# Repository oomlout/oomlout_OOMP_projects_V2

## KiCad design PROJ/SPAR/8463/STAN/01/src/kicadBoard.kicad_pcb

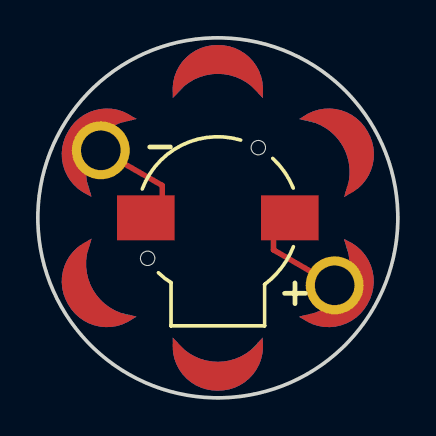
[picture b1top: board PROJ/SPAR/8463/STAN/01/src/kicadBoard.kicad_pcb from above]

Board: 2 copper layers, 20.0 x 20.0 mm, 8 parts (1 on the bottom side), 2 nets.

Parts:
B1: Buzzer; BUZZER-CCV
U$1, U$4, U$6, U$7: SEWTAP-NOHOLE2; PETAL-NOHOLE-2SIDE
U$2: LOGO-LPLP; LOGO-LILYPAD
U$8, U$9: SEWTAP6; PETAL-SMALL-2SIDE

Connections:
+: B1.+, U$9.1
-: B1.-, U$8.1

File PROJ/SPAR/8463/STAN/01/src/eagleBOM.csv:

"Part";"Value";"Device";"Package";"Description";"";
"B1";"Buzzer";"BUZZERSMD2";"BUZZER-CCV";"Buzzer 12mm";"";
"U$1";"SEWTAP-NOHOLE2";"SEWTAP-NOHOLE2";"PETAL-NOHOLE-2SIDE";"";"";
"U$2";"LOGO-LPLP";"LOGO-LPLP";"LOGO-LILYPAD";"";"";
"U$4";"SEWTAP-NOHOLE2";"SEWTAP-NOHOLE2";"PETAL-NOHOLE-2SIDE";"";"";
"U$6";"SEWTAP-NOHOLE2";"SEWTAP-NOHOLE2";"PETAL-NOHOLE-2SIDE";"";"";
"U$7";"SEWTAP-NOHOLE2";"SEWTAP-NOHOLE2";"PETAL-NOHOLE-2SIDE";"";"";
"U$8";"SEWTAP6";"SEWTAP6";"PETAL-SMALL-2SIDE";"";"";
"U$9";"SEWTAP6";"SEWTAP6";"PETAL-SMALL-2SIDE";"";"";

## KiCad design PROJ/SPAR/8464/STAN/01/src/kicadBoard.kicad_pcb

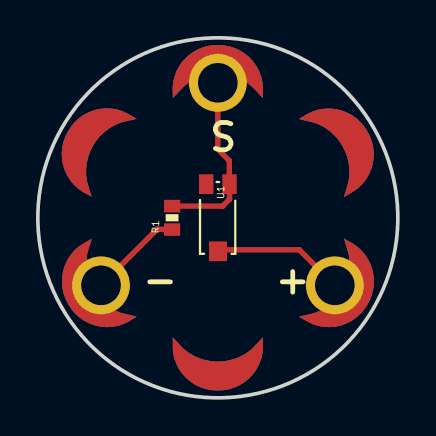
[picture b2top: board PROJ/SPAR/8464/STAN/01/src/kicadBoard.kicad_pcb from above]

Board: 2 copper layers, 20.0 x 20.0 mm, 9 parts (1 on the bottom side), 3 nets.

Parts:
LIGHT1, LIGHT2, LIGHT3: SEWTAP-NOHOLE2; PETAL-NOHOLE-2SIDE
LIGHT+0: SEWTAP6; PETAL-SMALL-2SIDE
LIGHT-0: SEWTAP6; PETAL-SMALL-2SIDE
LIGHTS0: SEWTAP6; PETAL-SMALL-2SIDE
R1: 10K; 0402-RES
U1: TEMT6000; TEMT6000-SEN
U$2: LOGO-LPLP; LOGO-LILYPAD

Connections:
+: LIGHT+0.1, U1.COLLECTOR
-: LIGHT-0.1, R1.1
S: LIGHTS0.1, R1.2, U1.EMITTER

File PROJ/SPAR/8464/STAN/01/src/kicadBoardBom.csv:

"Id";"Designator";"Package";"Quantity";"Designation";"Supplier and ref";
1;"LIGHT2,LIGHT1,LIGHT3";"PETAL-NOHOLE-2SIDE";3;"SEWTAP-NOHOLE2";;;
2;"R1";"0402-RES";1;"10K";;;
3;"U1";"TEMT6000-SEN";1;"TEMT6000";;;
4;"LIGHTS0,LIGHT+0,LIGHT-0";"PETAL-SMALL-2SIDE";3;"SEWTAP6";;;
5;"U$2";"LOGO-LILYPAD";1;"LOGO-LPLP";;;

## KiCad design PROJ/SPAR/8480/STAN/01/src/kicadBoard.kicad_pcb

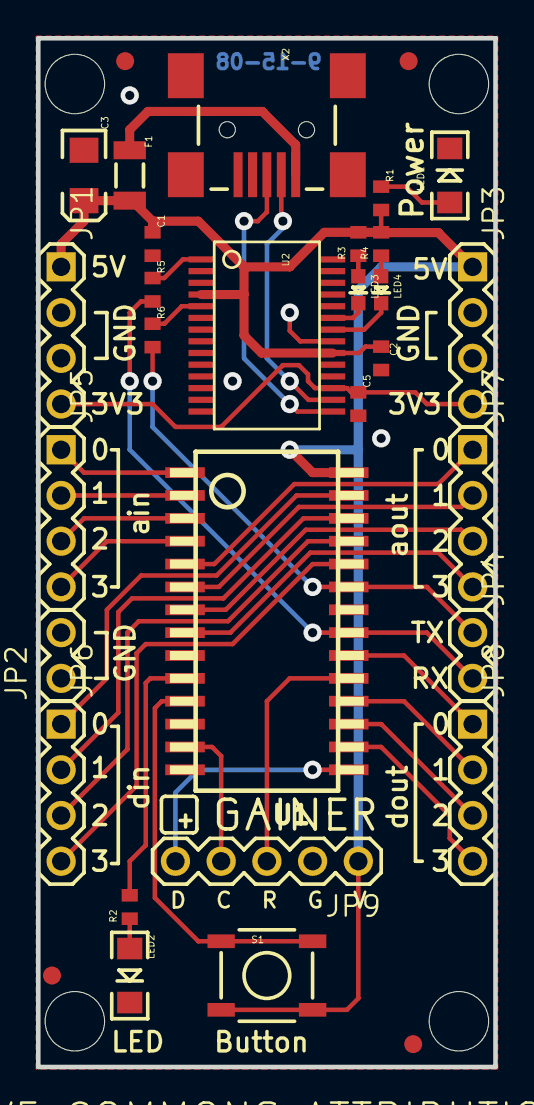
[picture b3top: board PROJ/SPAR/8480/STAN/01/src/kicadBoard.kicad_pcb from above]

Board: 2 copper layers, 25.4 x 57.1 mm, 39 parts (1 on the bottom side), 37 nets.

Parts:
C1, C2, C5: 0.1uF; C0402
C3: 10uF; EIA3216
E$1, E$2: FIDUCIAL-1X2
F1: PTC; PTC-1206
JP1, JP3: 1X04
JP2, JP4: 1X02
JP5: AIN; 1X04
JP6: DIN; 1X04
JP7: AOUT; 1X04
JP8: DOUT; 1X04
JP9: ISSP; 1X05
LED1: Power; LED-1206
LED2: LED-1206
LED3: TX; LED-0603
LED4: RX; LED-0603
R1, R3, R4, R5, R6: 1K; C0402
R2: 330; C0402
S1: TACTILE_SWITCH_SMD
U1: CY8C29466-24SOIC; SOIC28
U2: FT232RL; SSOP28DB
U$1: LOGO-SFENEW; SFE-NEW-WEBLOGO
U$10, U$17: FIDUCIAL1X2; FIDUCIAL-1X2
U$12, U$13, U$14, U$15: STAND-OFF
U$18: CREATIVE_COMMONS
U$19: GAINER_LOGO
X2: USBSMD; USB-MINIB

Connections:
3.3V: C5.1, JP1.4, JP3.4, U2.17
5V: C1.1, C2.1, C3.A, F1.2, JP1.1, JP3.1, JP9.1, R1.2, R3.2, R4.2, S1.3, S1.4, U1.28, U2.4, U2.20
AIN1: JP5.1, U1.1
AIN2: JP5.2, U1.2
AIN3: JP5.3, U1.3
AIN4: JP5.4, U1.4
AOUT1: JP7.1, U1.5
AOUT2: JP7.2, U1.6
AOUT3: JP7.3, U1.7
AOUT4: JP7.4, U1.8
DIN1: JP6.1, U1.27
DIN2: JP6.2, U1.26
DIN3: JP6.3, U1.25
DIN4: JP6.4, U1.24
DOUT1: JP8.1, U1.20
DOUT2: JP8.2, U1.18
DOUT3: JP8.3, U1.17
DOUT4: JP8.4, U1.16
GND: C1.2, C2.2, C3.C, C5.2, JP1.2, JP1.3, JP2.1, JP2.2, JP3.2, JP3.3, JP9.2, LED1.C, LED2.C, U1.14, U2.7, U2.18, U2.21, U2.25, U2.26, X2.GND
I2CSCL: JP9.4, U1.13
I2CSDA: JP9.5, U1.15
unnamed: LED3.A, R3.1
unnamed: F1.1, X2.VBUS
unnamed: LED1.A, R1.1
unnamed: LED4.A, R4.1
unnamed: R6.1, U2.5
unnamed: LED4.C, U2.22
unnamed: S1.1, S1.2, U1.11
unnamed: R2.2, U1.10
unnamed: LED2.A, R2.1
unnamed: U2.16, X2.D-
unnamed: U2.15, X2.D+
unnamed: R5.1, U2.1
unnamed: LED3.C, U2.23
RX: JP4.2, R5.2, U1.21
TX: JP4.1, R6.2, U1.23
XRES: JP9.3, U1.19

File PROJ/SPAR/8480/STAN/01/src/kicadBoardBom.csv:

"Id";"Designator";"Package";"Quantity";"Designation";"Supplier and ref";
1;"C2,C5,C1";"C0402";3;"0.1uF";;;
2;"U$13,U$15,U$12,U$14";"STAND-OFF";4;"STAND-OFF";;;
3;"JP1,JP3";"1X04";2;"";;;
4;"JP7";"1X04";1;"AOUT";;;
5;"R5,R1,R6,R3,R4";"C0402";5;"1K";;;
6;"R2";"C0402";1;"330";;;
7;"U$17,U$10";"FIDUCIAL-1X2";2;"FIDUCIAL1X2";;;
8;"LED2";"LED-1206";1;"";;;
9;"JP4,JP2";"1X02";2;"";;;
10;"U$18";"CREATIVE_COMMONS";1;"CREATIVE_COMMONS";;;
11;"JP8";"1X04";1;"DOUT";;;
12;"JP6";"1X04";1;"DIN";;;
13;"E$1,E$2";"FIDUCIAL-1X2";2;"";;;
14;"LED1";"LED-1206";1;"Power";;;
15;"X2";"USB-MINIB";1;"USBSMD";;;
16;"C3";"EIA3216";1;"10uF";;;
17;"U2";"SSOP28DB";1;"FT232RL";;;
18;"S1";"TACTILE_SWITCH_SMD";1;"";;;
19;"F1";"PTC-1206";1;"PTC";;;
20;"JP5";"1X04";1;"AIN";;;
21;"U$19";"GAINER_LOGO";1;"";;;
22;"LED4";"LED-0603";1;"RX";;;
23;"JP9";"1X05";1;"ISSP";;;
24;"LED3";"LED-0603";1;"TX";;;
25;"U1";"SOIC28";1;"CY8C29466-24SOIC";;;
26;"U$1";"SFE-NEW-WEBLOGO";1;"LOGO-SFENEW";;;

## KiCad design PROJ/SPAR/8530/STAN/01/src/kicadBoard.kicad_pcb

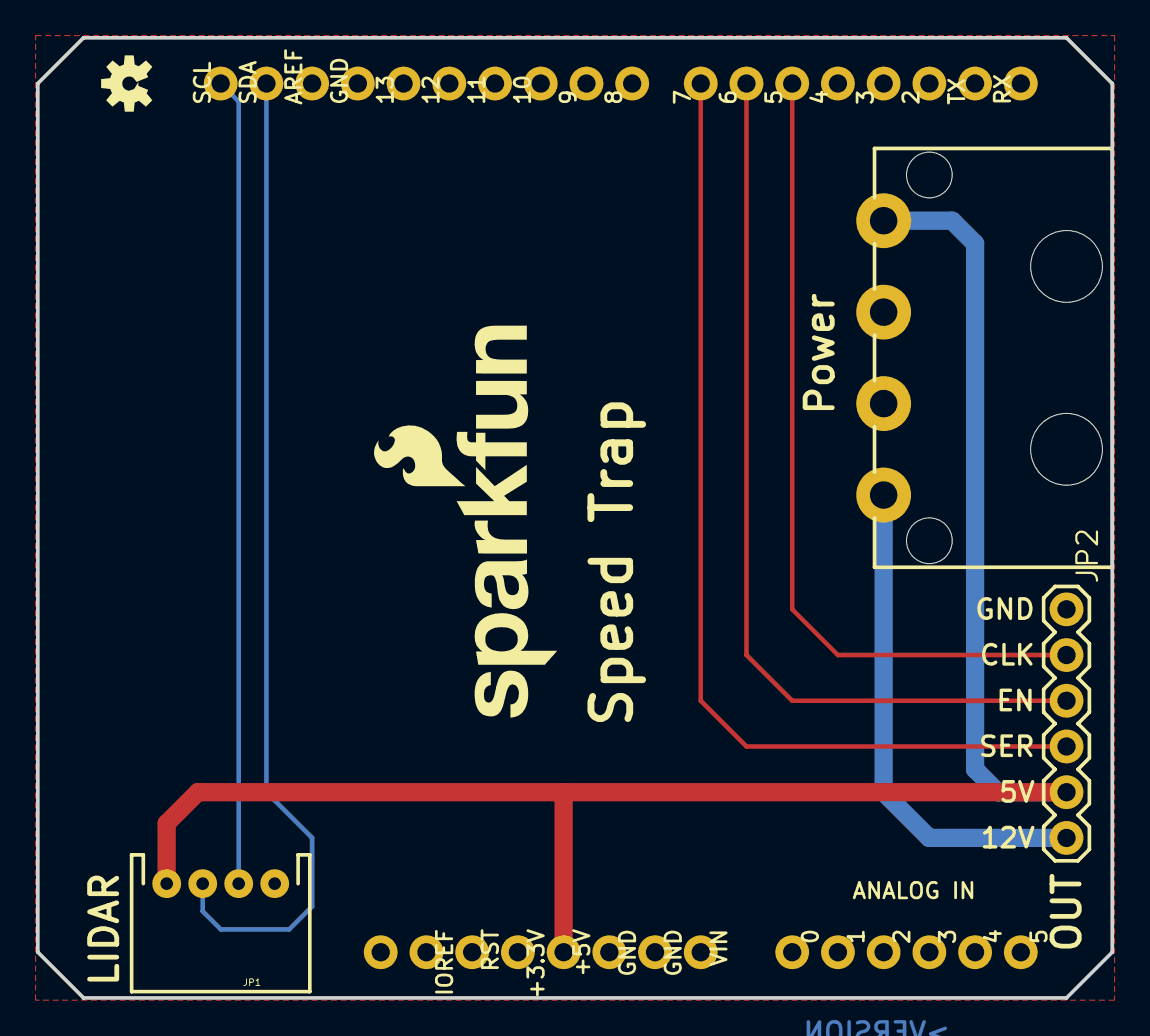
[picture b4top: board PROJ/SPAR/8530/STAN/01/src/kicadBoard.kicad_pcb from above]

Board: 2 copper layers, 59.7 x 53.3 mm, 7 parts (0 on the bottom side), 8 nets.

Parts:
FRAME1: CREATIVE_COMMONS
J1: ARDUINO_R3_SHIELD; UNO_R3_SHIELD
J2: Power; COMPUTER-PERIPHERAL-POWER-RA
JP1: LIDAR; JST-4-PTH
JP2: OUT; 1X06
LOGO1: SFE_LOGO_NAME_FLAME.2_INCH; SFE_LOGO_NAME_FLAME_.2
LOGO2: OSHW-LOGOS; OSHW-LOGO-S

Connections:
5V: J1.5V, J2.5V, JP1.4, JP2.5
12V: J2.12V, JP2.6
CLOCK: J1.D5, JP2.2
ENABLE: J1.D6, JP2.3
GND: J1.GND@0, J1.GND@1, J1.GND@2, J2.GND, JP1.1, JP2.1
SCL: J1.SCL, JP1.2
SDA: J1.SDA, JP1.3
SER_OUT: J1.D7, JP2.4

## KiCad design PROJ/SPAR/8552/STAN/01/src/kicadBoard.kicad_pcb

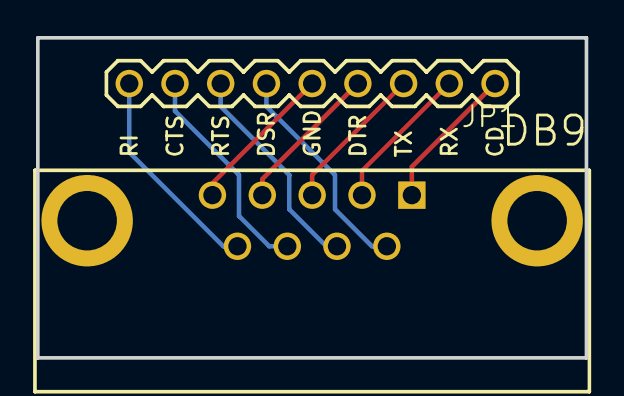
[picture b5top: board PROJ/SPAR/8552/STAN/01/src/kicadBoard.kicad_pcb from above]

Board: 2 copper layers, 30.5 x 17.8 mm, 3 parts (1 on the bottom side), 9 nets.

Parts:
DB9: DB9
JP1: M09; 1X09
U$2: LOGO-SFENEW; SFE-NEW-WEBLOGO

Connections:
CD: DB9.1, JP1.1
CTS: DB9.8, JP1.8
DSR: DB9.6, JP1.6
DTR: DB9.4, JP1.4
GND: DB9.5, JP1.5
RI: DB9.9, JP1.9
RTS: DB9.7, JP1.7
RX: DB9.2, JP1.2
TX: DB9.3, JP1.3

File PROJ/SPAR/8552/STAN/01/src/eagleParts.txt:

Partlist

Exported from boardEagle.brd at 20/08/2022 21:27

EAGLE Version 9.6.2 Copyright (c) 1988-2020 Autodesk, Inc.

Assembly variant: 

Part     Value          Package  Library  Position (inch)       Orientation

DB9                     DB9      SparkFun (0.6 0.3)             R180
JP1      M09            1X09     SparkFun (1 0.6)               R180

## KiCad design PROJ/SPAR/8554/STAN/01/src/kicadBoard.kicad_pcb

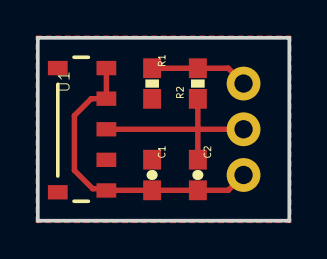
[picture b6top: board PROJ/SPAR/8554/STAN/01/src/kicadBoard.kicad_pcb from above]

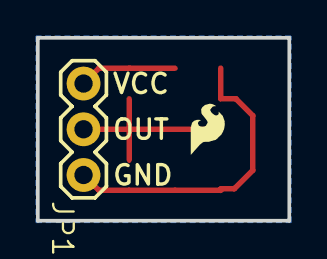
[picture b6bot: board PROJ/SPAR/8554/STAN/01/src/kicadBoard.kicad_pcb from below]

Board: 2 copper layers, 14.0 x 10.2 mm, 7 parts (2 on the bottom side), 4 nets.

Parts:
C1: 1uF; 0603-CAP
C2: 47nF; 0603-CAP
JP1: 1X03
R1: 100; 0603-RES
R2: 2.2k; 0603-RES
U1: IRRECEIVERSMD; TSOP8523
U$1: LOGO-SFESK; SFE-LOGO-FLAME

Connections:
GND: C1.2, C2.2, JP1.1, U1.1, U1.4, U1.5
OUT: C2.1, JP1.2, R2.1, U1.3
VCC: JP1.3, R1.1, R2.2
VS: C1.1, R1.2, U1.2

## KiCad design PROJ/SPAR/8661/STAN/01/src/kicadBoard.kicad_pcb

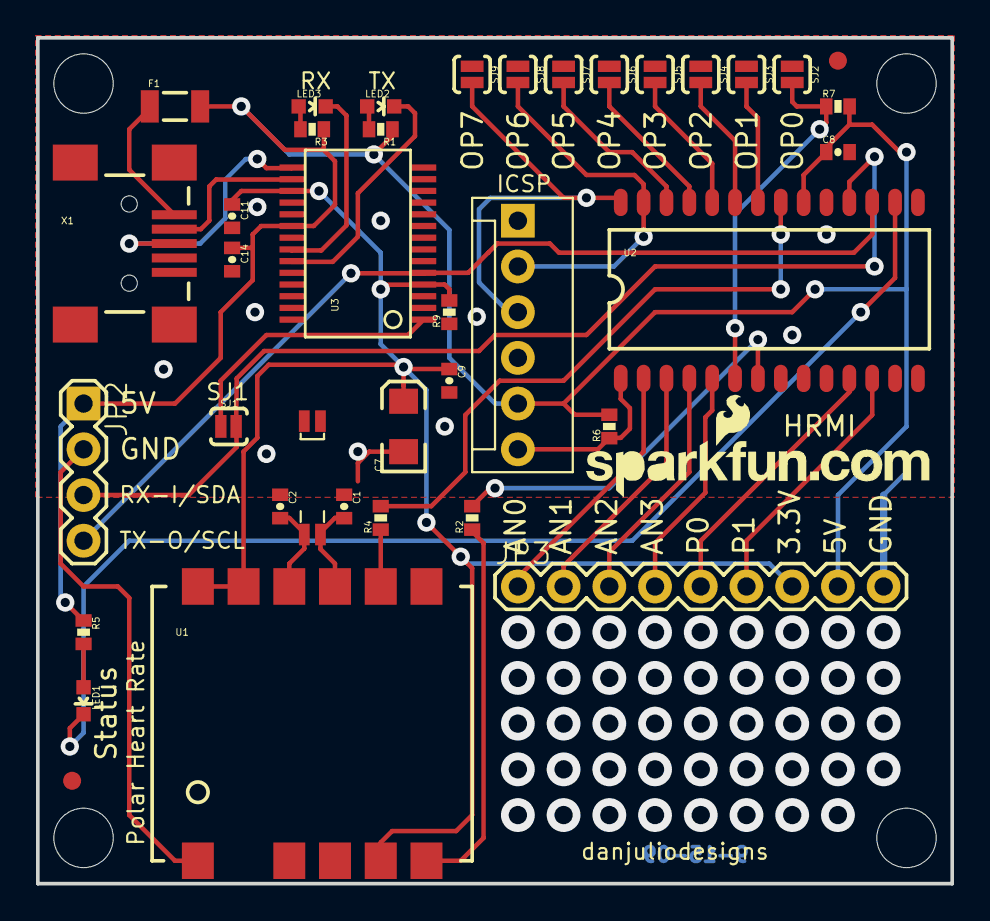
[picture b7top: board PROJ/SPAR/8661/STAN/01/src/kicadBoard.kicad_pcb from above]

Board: 2 copper layers, 50.8 x 47.0 mm, 43 parts (0 on the bottom side), 36 nets.

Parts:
C1, C2: 9pF; 0402-CAP
C7: 10uF; EIA3216
C8, C9, C11, C14: 0.1uF; 0402-CAP
F1: 500mA-PTC; PTC-1206
JP2: 1X04
JP3: M09; 1X09
LED1, LED3: Green; LED-0603
LED2: Red; LED-0603
Q1: 32kHz; CRYSTAL-32KHZ-SMD_EPSON_MC146
R1, R3, R5: 750; 0402-RES
R2, R4: 1K; 0402-RES
R6, R7: 10K; 0402-RES
R9: 330; 0402-RES
SJ1: SOLDERJUMPERNC2; SJ_2S-NOTRACE
SJ2, SJ3, SJ4, SJ5, SJ6, SJ7, SJ8, SJ9: SOLDERJUMPERNO; SJ_2S-NO
U1: RMCM01
U2: PIC16F913; SO-28W
U3: FT232RL-BASICSSOP; SSOP28DB
U10: PIC-ICSPPTH; MOLEX-1X6
U$1: LOGO-SFENEW; SFE-NEW-WEBLOGO
U$4, U$8: FIDUCIAL1X2; FIDUCIAL-1X2
U$13, U$15, U$16, U$17: STAND-OFF
X1: USBSMD; USB-MINIB

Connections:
3.3V: C7.A, C9.1, C11.1, JP3.7, R9.2, U1.1, U1.2, U1.8, U3.4, U3.17
5V: C8.1, C14.1, F1.2, JP2.1, JP3.8, R1.1, R3.1, R5.1, R6.2, R7.2, U2.20, U3.20, U10.5
AN0: JP3.1, U2.2
AN1: JP3.2, U2.3
AN2: JP3.3, U2.4
AN3: JP3.4, U2.5
GND: C1.1, C2.1, C7.C, C8.2, C9.2, C11.2, C14.2, JP2.2, JP3.9, R9.1, SJ2.1, SJ3.1, SJ4.1, SJ5.1, SJ6.1, SJ7.1, SJ8.1, SJ9.1, U1.11, U2.8, U2.19, U3.7, U3.18, U3.21, U3.25, U3.26, U10.4, X1.GND
HR: R4.2, U2.21
unnamed: LED2.A, R1.2
unnamed: U3.16, X1.D-
unnamed: LED3.A, R3.2
unnamed: U3.15, X1.D+
unnamed: LED1.A, R5.2
unnamed: R4.1, U1.5
unnamed: R2.1, U1.7
unnamed: C1.2, Q1.P$1, U1.4
unnamed: C2.2, Q1.P$2, U1.3
OP0: R7.1, SJ2.2, U2.6
OP1: SJ3.2, U2.22
OP2: SJ4.2, U2.23
OP3: SJ5.2, U2.24
OP4: SJ6.2, U2.25
OP5: SJ7.2, U2.26
P0: JP3.5, U2.11
P1: JP3.6, U2.12
PGC: SJ8.2, U2.27, U10.2
PGD: SJ9.2, U2.28, U10.3
RST: R2.2, U2.7
RX: JP2.4, U2.17, U3.5
RXLED: LED3.C, U3.22
STAT: LED1.C, U2.16
TX: JP2.3, SJ1.2, U2.18
TXLED: LED2.C, U3.23
USB-TX: SJ1.1, U3.1
VBUS: F1.1, X1.VBUS
VPP: R6.1, U2.1, U10.6

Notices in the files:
parts and their libraries:
HTTP://CREATIVECOMMONS.ORG/LICENSES/BY-SA/3.0
RELEASED UNDER THE CREATIVE COMMONS ATTRIBUTION SHARE-ALIKE 3.0 LICENSE
RELEASED UNDER THE CREATIVE COMMONS ATTRIBUTION SHARE-ALIKE 4.0 LICENSE
HTTPS://CREATIVECOMMONS.ORG/LICENSES/BY-SA/4.0
